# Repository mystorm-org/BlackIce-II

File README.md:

# BlackIce-II

Project documentation can be found in the [project wiki](https://github.com/mystorm-org/BlackIce-II/wiki).

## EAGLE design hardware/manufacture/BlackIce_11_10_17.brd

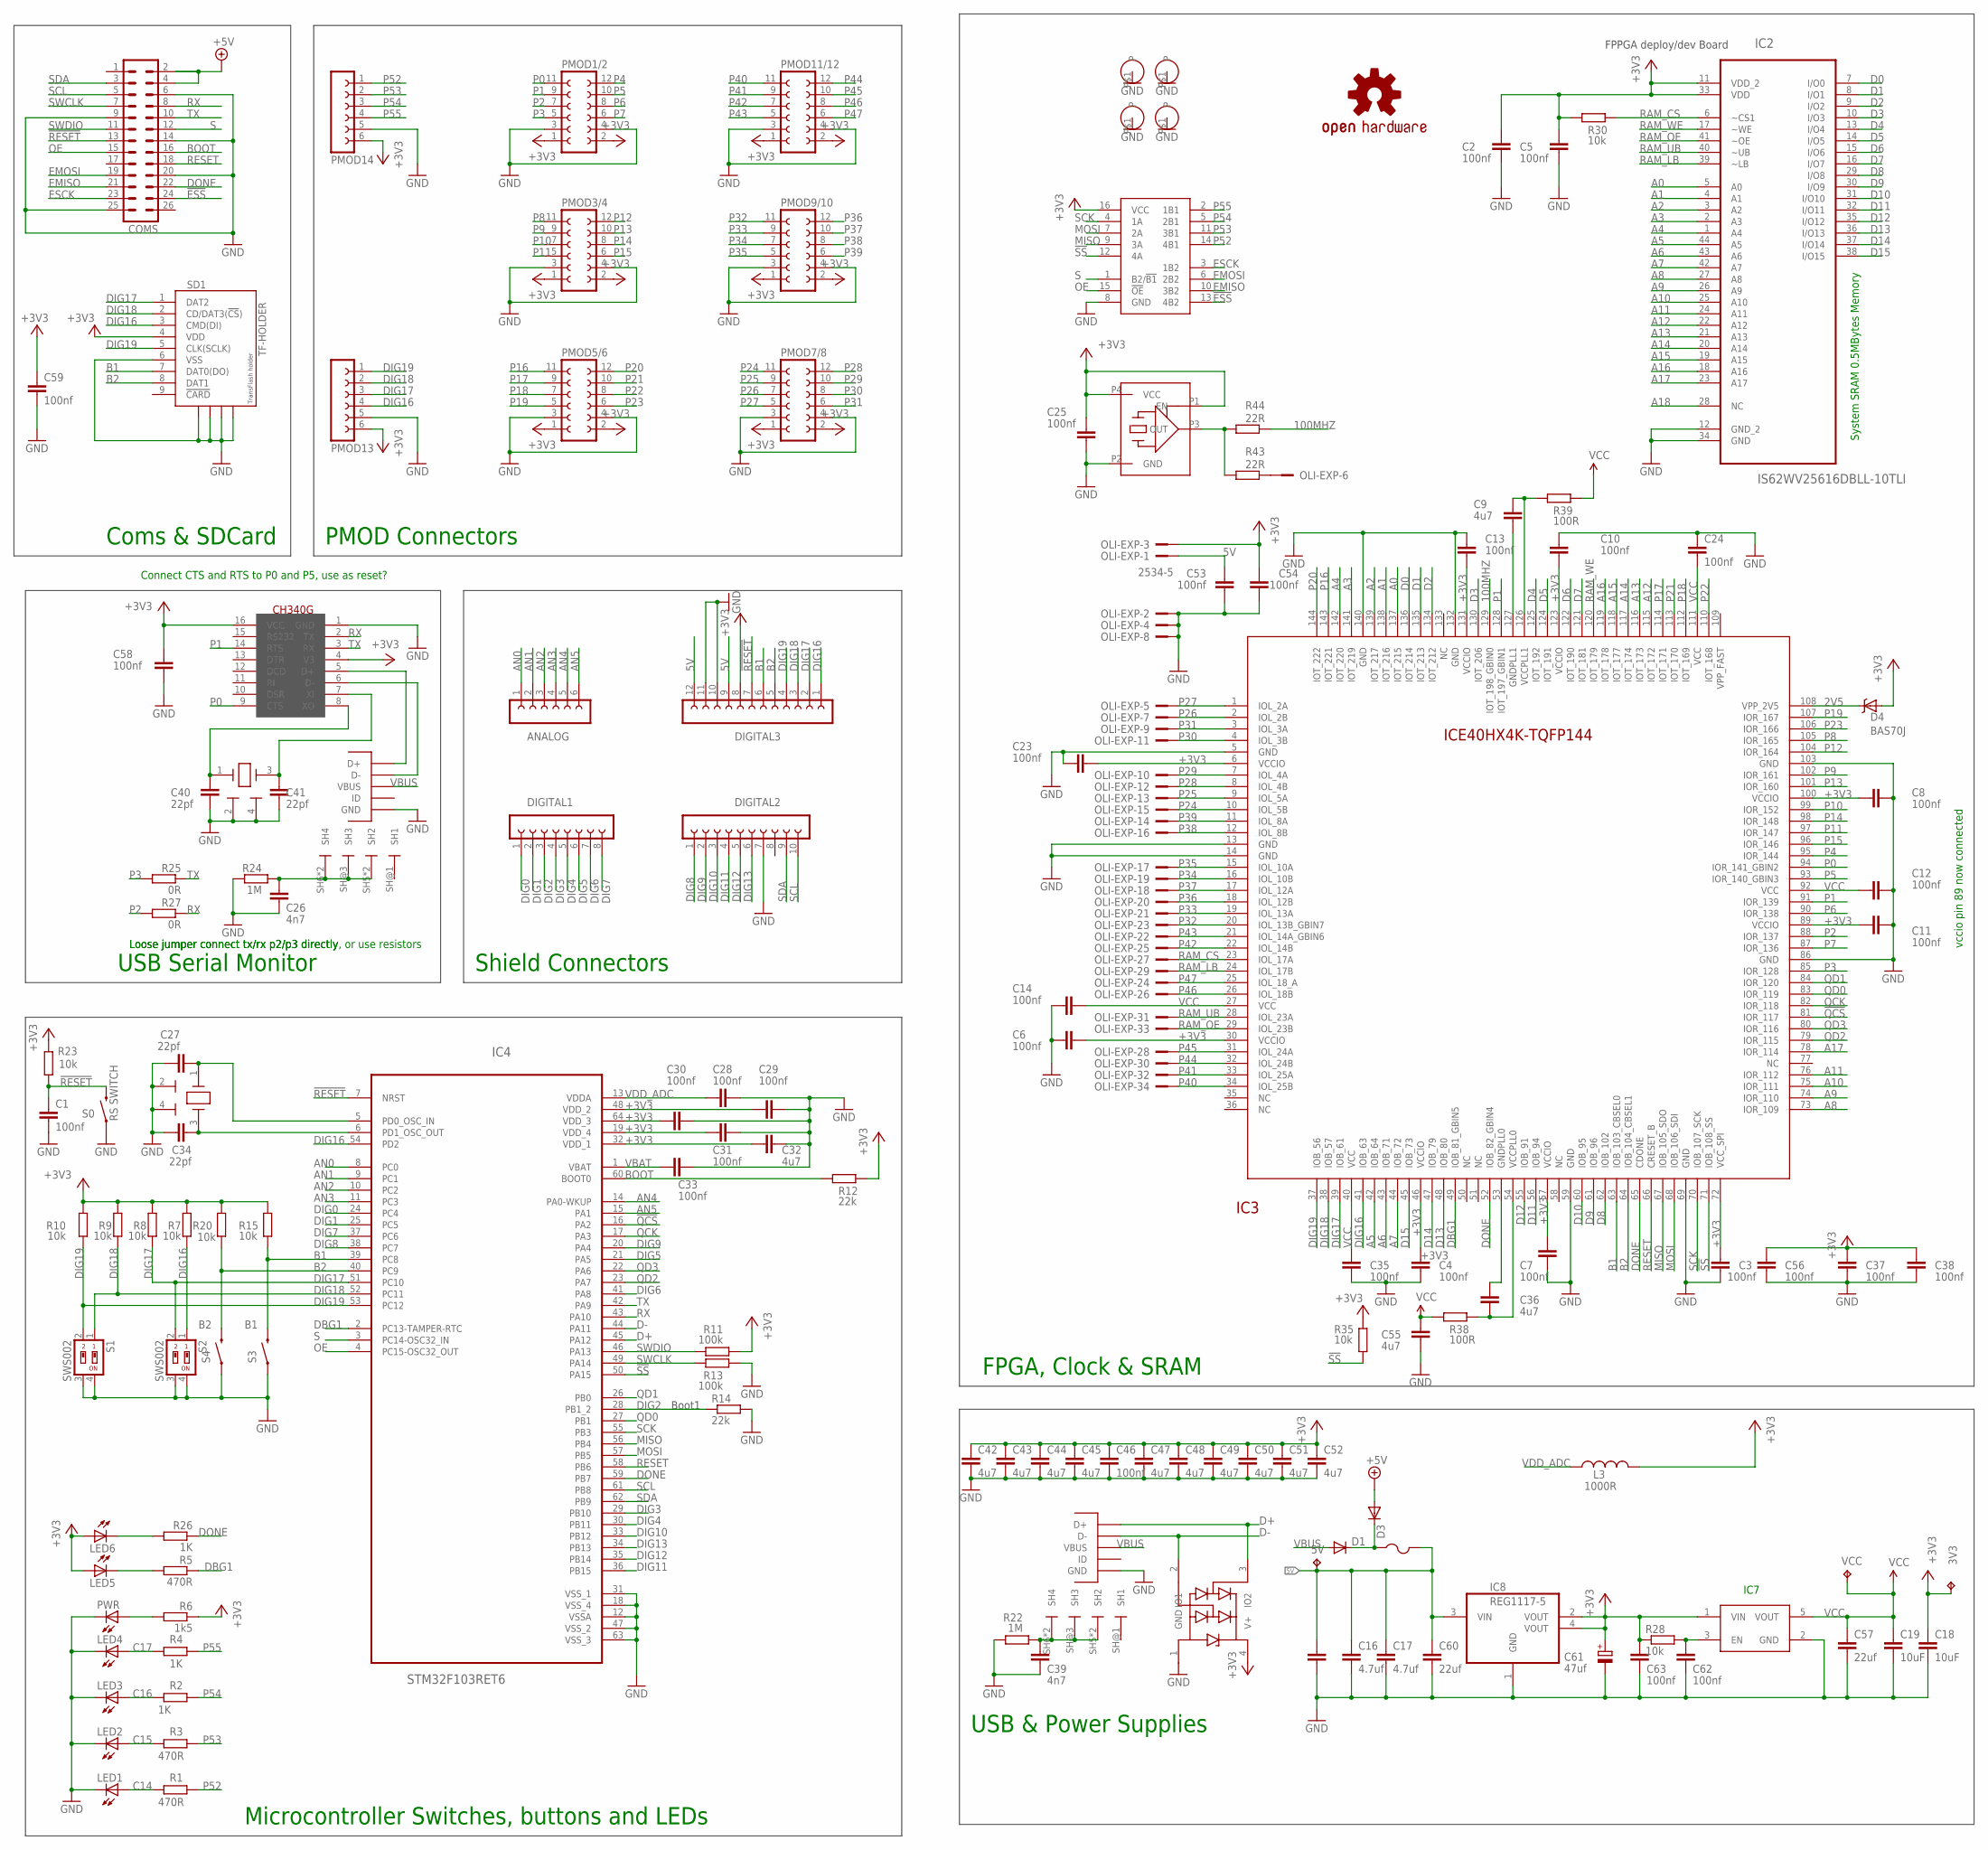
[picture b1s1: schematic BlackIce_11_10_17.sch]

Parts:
3V3, 5V: TPB1,27; B1,27
ANALOG: FE06-1; FE06
C1, C2, C3, C4, C5, C6, C7, C8, C10, C11, C12, C13, C14, C23, C24, C25, C28, C29, C30, C31, C33, C35, C37, C38, C46, C53, C54, C56, C58, C59, C62, C63: 100nf; C0402
C9, C32, C36, C42, C43, C44, C45, C47, C48, C49, C50, C51, C52, C55: 4u7; C0402
C16, C17: 4.7uf; C0402
C18, C19: 10uF; C0603
C20: 47uF; 1206
C26, C39: 4n7; C0402
C27, C34, C40, C41: 22pf; C0402
C57, C60: 22uf; C0603
C61: 47uf; R/2012-12W
COM: FCI-MICROUSB-B-PEG; MICROUSB-B-PEG
COMS: MA13-2
D1, D3: DIODE-SOD123; SOD123
D4: BAS70J; SOD-323
DIGITAL1: FE08-1; FE08
DIGITAL2: FE10-1; FE10
DIGITAL3: FE12-1; FE12
ESD1: PRTR5V0U2X; SOT143B
F1: PTCFUSE-1206; R1206
IC1: CH340G; SOIC16
IC2: IS62WV25616DBLL-10TLI; SOP80P1176X120-44N
IC3: ICE40HX4K_TQFP144; TQFP144
IC4: STM32F103RET6; QFP50P1200X1200X160-64N
IC6: 74CBTLV3257; TSSOP-16
IC7: NCP114; TSOP-5/SOT23-5
IC8: REG1117-5; SOT223
L3: 1000R; C0402
LED1, LED2, LED3, LED4, LED5, LED6: LEDCHIPLED_0603; CHIPLED_0603
OLI-EXP: 2534-5; PAK100/2500-5-34
OSHW: OSHW-LOGOL; OSHW-LOGO-L
PMOD1/2, PMOD3/4, PMOD5/6, PMOD7/8, PMOD9/10, PMOD11/12: FE06-2W
PMOD13, PMOD14: FE06W
PWR: LEDCHIPLED_0603; CHIPLED_0603
R1, R3, R5: 470R; R0402
R2, R4, R26: 1K; R0402
R6: 1k5; R0402
R7, R8, R9, R10, R15, R20, R23, R28, R30, R35: 10k; R0402
R11, R13: 100k; R0402
R12, R14: 22k; R0402
R22, R24: 1M; R0402
R25, R27: 0R; R0402
R38, R39: 100R; R0402
R43, R44: 22R; R0402
S0: RS SWITCH; TACTILE-SWITCH-1101NE
S1, S2: SWS002; SMS-002
S3, S4: SWITCH-MOMENTARY-2SMD-1101NE; TACTILE-SWITCH-1101NE
SD1: TF-HOLDER; TF-PULL
U$2: FCI-MICROUSB-B-PEG; MICROUSB-B-PEG
U$16, U$21, U$22, U$24: HOLE-2.5MM; 2.5MM-HOLE
VCC: TPB1,27; B1,27
X1: TXC-7W-20.000MBB-T; XTAL-7X5
Y1: 12MZ; CRYSTAL-3.2X2.5
Y2: 12Mz; CRYSTAL-3.2X2.5

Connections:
2V5: D4.C, IC3.108 (VPP_2V5)
5V: 5V.TP, C16.1, C17.1, C20.1, C53.1, C60.1, DIGITAL3.9, DIGITAL3.12, F1.2, IC8.3 (VIN), OLI-EXP.1
100MHZ: IC3.129 (IOT_198_GBIN0), R44.2
!ESS: COMS.24, IC6.13 (4B2)
!QCS: IC3.81 (IOR_117), IC4.16 (PA2)
!RESET: C1.1, COMS.13, DIGITAL3.7, IC4.7 (NRST), R23.1, S0.2
!SS: IC3.71 (IOB_108_SS), IC4.50 (PA15), IC6.12 (4A), R35.2
+3V3: 3V3.TP, C2.1, C3.1, C4.1, C5.1, C6.2, C7.1, C8.1, C10.2, C11.1, C13.1, C18.1, C23.1, C25.2, C29.2, C30.2, C31.2, C32.2, C37.1, C38.1, C42.1, C43.1, C44.1, C45.1, C46.1, C47.1, C48.1, C49.1, C50.1, C51.1, C52.1, C54.1, C56.1, C58.2, C59.1, C61.+, C63.2, D4.A, DIGITAL3.8, ESD1.4 (V+), IC1.4 (V3), IC1.16 (VCC), IC2.11 (VDD_2), IC2.33 (VDD), IC3.6 (VCCIO), IC3.30 (VCCIO), IC3.46 (VCCIO), IC3.57 (VCCIO), IC3.72 (VCC_SPI), IC3.89 (VCCIO), IC3.100 (VCCIO), IC3.123 (VCCIO), IC3.131 (VCCIO), IC4.19 (VDD_4), IC4.32 (VDD_1), IC4.48 (VDD_2), IC4.64 (VDD_3), IC6.16 (VCC), IC7.1 (VIN), IC8.2 (VOUT), IC8.4 (VOUT), L3.1, LED5.A, LED6.A, OLI-EXP.3, PMOD1/2.1, PMOD1/2.2, PMOD3/4.1, PMOD3/4.2, PMOD5/6.1, PMOD5/6.2, PMOD7/8.1, PMOD7/8.2, PMOD9/10.1, PMOD9/10.2, PMOD11/12.1, PMOD11/12.2, PMOD13.6, PMOD14.6, R6.1, R7.2, R8.2, R9.2, R10.2, R11.1, R12.2, R15.2, R20.2, R23.2, R28.1, R30.2, R35.1, SD1.4 (VDD), X1.P1 (EN), X1.P4 (VCC)
+5V: COMS.2, COMS.4, D3.A
A0: IC2.5 (A0), IC3.137 (IOT_215)
A1: IC2.4 (A1), IC3.138 (IOT_216)
A2: IC2.3 (A2), IC3.139 (IOT_217)
A3: IC2.2 (A3), IC3.141 (IOT_219)
A4: IC2.1 (A4), IC3.142 (IOT_220)
A5: IC2.44 (A5), IC3.42 (IOB_64)
A6: IC2.43 (A6), IC3.43 (IOB_71)
A7: IC2.42 (A7), IC3.44 (IOB_72)
A8: IC2.27 (A8), IC3.73 (IOR_109)
A9: IC2.26 (A9), IC3.74 (IOR_110)
A10: IC2.25 (A10), IC3.75 (IOR_111)
A11: IC2.24 (A11), IC3.76 (IOR_112)
A12: IC2.22 (A12), IC3.115 (IOT_172)
A13: IC2.21 (A13), IC3.116 (IOT_173)
A14: IC2.20 (A14), IC3.117 (IOT_174)
A15: IC2.19 (A15), IC3.118 (IOT_177)
A16: IC2.18 (A16), IC3.119 (IOT_178)
A17: IC2.23 (A17), IC3.78 (IOR_114)
A18: IC2.28 (NC)
AN0: ANALOG.1, IC4.8 (PC0)
AN1: ANALOG.2, IC4.9 (PC1)
AN2: ANALOG.3, IC4.10 (PC2)
AN3: ANALOG.4, IC4.11 (PC3)
AN4: ANALOG.5, IC4.14 (PA0-WKUP)
AN5: ANALOG.6, IC4.15 (PA1)
B1: DIGITAL3.6, IC3.63 (IOB_103_CBSEL0), IC4.39 (PC8), R15.1, S3.2, SD1.7 (DAT0(DO))
B2: DIGITAL3.5, IC3.64 (IOB_104_CBSEL1), IC4.40 (PC9), R20.1, S4.2, SD1.8 (DAT1)
BOOT: COMS.16, IC4.60 (BOOT0), R12.1
C14: LED1.A, R1.1
C15: LED2.A, R3.1
C16: LED3.A, R2.1
C17: LED4.A, R4.1
D0: IC2.7 (I/O0), IC3.136 (IOT_214)
D1: IC2.8 (I/O1), IC3.135 (IOT_213)
D2: IC2.9 (I/O2), IC3.134 (IOT_212)
D3: IC2.10 (I/O3), IC3.130 (IOT_206)
D4: IC2.13 (I/O4), IC3.125 (IOT_192)
D5: IC2.14 (I/O5), IC3.124 (IOT_191)
D6: IC2.15 (I/O6), IC3.122 (IOT_190)
D7: IC2.16 (I/O7), IC3.121 (IOT_181)
D8: IC2.29 (I/O8), IC3.62 (IOB_102)
D9: IC2.30 (I/O9), IC3.61 (IOB_96)
D10: IC2.31 (I/O10), IC3.60 (IOB_95)
D11: IC2.32 (I/O11), IC3.56 (IOB_94)
D12: IC2.35 (I/O12), IC3.55 (IOB_91)
D13: IC2.36 (I/O13), IC3.48 (IOB_80)
D14: IC2.37 (I/O14), IC3.47 (IOB_79)
D15: IC2.38 (I/O15), IC3.45 (IOB_73)
D+: ESD1.3 (IO2), IC4.45 (PA12), U$2.P$3 (D+)
D-: ESD1.2 (IO1), IC4.44 (PA11), U$2.P$2 (D-)
DBG1: IC3.49 (IOB_81_GBIN5), IC4.2 (PC13-TAMPER-RTC), R5.1
DIG0: DIGITAL1.1, IC4.24 (PC4)
DIG1: DIGITAL1.2, IC4.25 (PC5)
DIG2: DIGITAL1.3, IC4.28 (PB1_2), R14.1
DIG3: DIGITAL1.4, IC4.29 (PB10)
DIG4: DIGITAL1.5, IC4.30 (PB11)
DIG5: DIGITAL1.6, IC4.21 (PA5)
DIG6: DIGITAL1.7, IC4.41 (PA8)
DIG7: DIGITAL1.8, IC4.37 (PC6)
DIG8: DIGITAL2.1, IC4.38 (PC7)
DIG9: DIGITAL2.2, IC4.20 (PA4)
DIG10: DIGITAL2.3, IC4.33 (PB12)
DIG11: DIGITAL2.4, IC4.36 (PB15)
DIG12: DIGITAL2.5, IC4.35 (PB14)
DIG13: DIGITAL2.6, IC4.34 (PB13)
DIG16: DIGITAL3.1, IC3.41 (IOB_63), IC4.54 (PD2), PMOD13.4, R7.1, S2.1, SD1.3 (CMD(DI))
DIG17: DIGITAL3.2, IC3.39 (IOB_61), IC4.51 (PC10), PMOD13.3, R8.1, S2.2, SD1.1 (DAT2)
DIG18: DIGITAL3.3, IC3.38 (IOB_57), IC4.52 (PC11), PMOD13.2, R9.1, S1.1, SD1.2 (CD/DAT3(!CS!))
DIG19: DIGITAL3.4, IC3.37 (IOB_56), IC4.53 (PC12), PMOD13.1, R10.1, S1.2, SD1.5 (CLK(SCLK))
DONE: COMS.22, IC3.52 (IOB_82_GBIN4), IC3.65 (CDONE), IC4.59 (PB7), R26.1
EMISO: COMS.21, IC6.10 (3B2)
EMOSI: COMS.19, IC6.6 (2B2)
ESCK: COMS.23, IC6.3 (1B2)
GND: C1.2, C2.2, C3.2, C4.2, C5.2, C6.1, C7.2, C8.2, C10.1, C11.2, C12.2, C13.2, C14.2, C16.2, C17.2, C18.2, C19.2, C20.2, C23.2, C24.1, C25.1, C26.1, C27.1, C28.1, C29.1, C30.1, C31.1, C32.1, C33.1, C34.1, C35.2, C37.2, C38.2, C39.1, C40.1, C41.1, C42.2, C43.2, C44.2, C45.2, C46.2, C47.2, C48.2, C49.2, C50.2, C51.2, C52.2, C53.2, C54.2, C55.2, C56.2, C57.2, C58.1, C59.2, C60.2, C61.-, C62.1, C63.1, COM.P$5 (GND), COMS.6, COMS.9, COMS.14, COMS.20, COMS.25, DIGITAL2.7, DIGITAL3.10, DIGITAL3.11, ESD1.1 (GND), IC1.1 (GND), IC2.12 (GND_2), IC2.34 (GND), IC3.5 (GND), IC3.13 (GND), IC3.14 (GND), IC3.59 (GND), IC3.69 (GND), IC3.86 (GND), IC3.103 (GND), IC3.132 (GND), IC3.140 (GND), IC4.12 (VSSA), IC4.18 (VSS_4), IC4.31 (VSS_1), IC4.47 (VSS_2), IC4.63 (VSS_3), IC6.8 (GND), IC7.2 (GND), IC8.1 (GND), LED1.C, LED2.C, LED3.C, LED4.C, OLI-EXP.2, OLI-EXP.4, OLI-EXP.8, PMOD1/2.3, PMOD1/2.4, PMOD3/4.3, PMOD3/4.4, PMOD5/6.3, PMOD5/6.4, PMOD7/8.3, PMOD7/8.4, PMOD9/10.3, PMOD9/10.4, PMOD11/12.3, PMOD11/12.4, PMOD13.5, PMOD14.5, PWR.C, R13.1, R14.2, R22.2, R24.2, S0.1, S1.3, S1.4, S2.3, S2.4, S3.1, S4.1, SD1.6 (VSS), SD1.S1, SD1.S2, SD1.S3, SD1.S4, U$2.P$5 (GND), U$16.P$1, U$21.P$1, U$22.P$1, U$24.P$1, X1.P2 (GND), Y1.2 (GND), Y1.4 (GND), Y2.2 (GND), Y2.4 (GND)
MISO: IC3.67 (IOB_105_SDO), IC4.56 (PB4), IC6.9 (3A)
MOSI: IC3.68 (IOB_106_SDI), IC4.57 (PB5), IC6.7 (2A)
unnamed: PWR.A, R6.2
unnamed: LED5.C, R5.2
unnamed: C9.2, IC3.126 (VCCPLL1), R39.2
unnamed: C39.2, R22.1, U$2.SH5 (SH2), U$2.SH6 (SH4), U$2.SH@2 (SH2), U$2.SH@3 (SH3), U$2.SH@4 (SH4)
unnamed: C62.2, IC7.3 (EN), R28.2
unnamed: C36.1, IC3.53 (GNDPLL0)
unnamed: C34.2, IC4.6 (PD1_OSC_OUT), Y1.3 (X2)
unnamed: R43.1, R44.1, X1.P3 (OUT)
unnamed: D1.C, D3.C, F1.1
unnamed: COM.P$3 (D+), IC1.5 (D+)
unnamed: COM.P$2 (D-), IC1.6 (D-)
unnamed: C26.2, COM.SH5 (SH2), COM.SH6 (SH4), COM.SH@2 (SH2), COM.SH@3 (SH3), COM.SH@4 (SH4), R24.1
unnamed: C9.1, IC3.127 (GNDPLL1)
unnamed: OLI-EXP.6, R43.2
unnamed: C36.2, IC3.54 (VCCPLL0), R38.1
unnamed: C27.2, IC4.5 (PD0_OSC_IN), Y1.1 (X1)
unnamed: C41.2, IC1.7 (XI), Y2.3 (X2)
unnamed: C40.2, IC1.8 (XO), Y2.1 (X1)
unnamed: LED6.C, R26.2
OE: COMS.15, IC4.4 (PC15-OSC32_OUT), IC6.15 (!OE)
P0: IC1.9 (CTS), IC3.94 (IOR_141_GBIN2), PMOD1/2.11
P1: IC1.14 (RTS), IC3.91 (IOR_139), IC3.128 (IOT_197_GBIN1), PMOD1/2.9
P2: IC3.88 (IOR_137), PMOD1/2.7, R27.2
P3: IC3.85 (IOR_128), PMOD1/2.5, R25.2
P4: IC3.95 (IOR_144), PMOD1/2.12
P5: IC3.93 (IOR_140_GBIN3), PMOD1/2.10
P6: IC3.90 (IOR_138), PMOD1/2.8
P7: IC3.87 (IOR_136), PMOD1/2.6
P8: IC3.105 (IOR_165), PMOD3/4.11
P9: IC3.102 (IOR_161), PMOD3/4.9
P10: IC3.99 (IOR_152), PMOD3/4.7
P11: IC3.97 (IOR_147), PMOD3/4.5
P12: IC3.104 (IOR_164), PMOD3/4.12
P13: IC3.101 (IOR_160), PMOD3/4.10
P14: IC3.98 (IOR_148), PMOD3/4.8
P15: IC3.96 (IOR_146), PMOD3/4.6
P16: IC3.143 (IOT_221), PMOD5/6.11
P17: IC3.114 (IOT_171), PMOD5/6.9
P18: IC3.112 (IOT_169), PMOD5/6.7
P19: IC3.107 (IOR_167), PMOD5/6.5
P20: IC3.144 (IOT_222), PMOD5/6.12
P21: IC3.113 (IOT_170), PMOD5/6.10
P22: IC3.110 (IOT_168), PMOD5/6.8
P23: IC3.106 (IOR_166), PMOD5/6.6
P24: IC3.10 (IOL_5B), OLI-EXP.15, PMOD7/8.11
P25: IC3.9 (IOL_5A), OLI-EXP.13, PMOD7/8.9
P26: IC3.2 (IOL_2B), OLI-EXP.7, PMOD7/8.7
P27: IC3.1 (IOL_2A), OLI-EXP.5, PMOD7/8.5
P28: IC3.8 (IOL_4B), OLI-EXP.12, PMOD7/8.12
P29: IC3.7 (IOL_4A), OLI-EXP.10, PMOD7/8.10
P30: IC3.4 (IOL_3B), OLI-EXP.11, PMOD7/8.8
P31: IC3.3 (IOL_3A), OLI-EXP.9, PMOD7/8.6
P32: IC3.20 (IOL_13B_GBIN7), OLI-EXP.23, PMOD9/10.11
P33: IC3.19 (IOL_13A), OLI-EXP.21, PMOD9/10.9
P34: IC3.16 (IOL_10B), OLI-EXP.19, PMOD9/10.7
P35: IC3.15 (IOL_10A), OLI-EXP.17, PMOD9/10.5
P36: IC3.18 (IOL_12B), OLI-EXP.20, PMOD9/10.12
P37: IC3.17 (IOL_12A), OLI-EXP.18, PMOD9/10.10
P38: IC3.12 (IOL_8B), OLI-EXP.16, PMOD9/10.8
P39: IC3.11 (IOL_8A), OLI-EXP.14, PMOD9/10.6
P40: IC3.34 (IOL_25B), OLI-EXP.34, PMOD11/12.11
P41: IC3.33 (IOL_25A), OLI-EXP.32, PMOD11/12.9
P42: IC3.22 (IOL_14B), OLI-EXP.25, PMOD11/12.7
P43: IC3.21 (IOL_14A_GBIN6), OLI-EXP.22, PMOD11/12.5
P44: IC3.32 (IOL_24B), OLI-EXP.30, PMOD11/12.12
P45: IC3.31 (IOL_24A), OLI-EXP.28, PMOD11/12.10
P46: IC3.26 (IOL_18B), OLI-EXP.26, PMOD11/12.8
P47: IC3.25 (IOL_18_A), OLI-EXP.24, PMOD11/12.6
P52: IC6.14 (4B1), PMOD14.1, R1.2
P53: IC6.11 (3B1), PMOD14.2, R3.2
P54: IC6.5 (2B1), PMOD14.3, R2.2
P55: IC6.2 (1B1), PMOD14.4, R4.2
QCK: IC3.82 (IOR_118), IC4.17 (PA3)
QD0: IC3.83 (IOR_119), IC4.27 (PB1)
QD1: IC3.84 (IOR_120), IC4.26 (PB0)
QD2: IC3.79 (IOR_115), IC4.23 (PA7)
QD3: IC3.80 (IOR_116), IC4.22 (PA6)
RAM_CS: IC2.6 (~CS1), IC3.23 (IOL_17A), OLI-EXP.27, R30.1
RAM_LB: IC2.39 (~LB), IC3.24 (IOL_17B), OLI-EXP.29
RAM_OE: IC2.41 (~OE), IC3.29 (IOL_23B), OLI-EXP.33
RAM_UB: IC2.40 (~UB), IC3.28 (IOL_23A), OLI-EXP.31
RAM_WE: IC2.17 (~WE), IC3.120 (IOT_179)
RESET: COMS.18, IC3.66 (CRESET_B), IC4.58 (PB6)
RX: COMS.8, IC1.2 (TX), IC4.43 (PA10), R27.1
S: COMS.12, IC4.3 (PC14-OSC32_IN), IC6.1 (B2/!B1)
SCK: IC3.70 (IOB_107_SCK), IC4.55 (PB3), IC6.4 (1A)
SCL: COMS.5, DIGITAL2.10, IC4.61 (PB8)
SDA: COMS.3, DIGITAL2.9, IC4.62 (PB9)
SWCLK: COMS.7, IC4.49 (PA14), R13.2
SWDIO: COMS.11, IC4.46 (PA13), R11.2
TX: COMS.10, IC1.3 (RX), IC4.42 (PA9), R25.1
VBAT: C33.2, IC4.1 (VBAT)
VBUS: COM.P$1 (VBUS), D1.A, U$2.P$1 (VBUS)
VCC: C12.1, C14.1, C19.1, C24.2, C35.1, C55.1, C57.1, IC3.27 (VCC), IC3.40 (VCC), IC3.92 (VCC), IC3.111 (VCC), IC7.5 (VOUT), R38.2, R39.1, VCC.TP
VDD_ADC: C28.2, IC4.13 (VDDA), L3.2

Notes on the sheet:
System SRAM 0.5MBytes Memory
FPPGA deploy/dev Board
Boot1
PMOD Connectors
Shield Connectors
Coms & SDCard
FPGA, Clock & SRAM
USB & Power Supplies
Microcontroller Switches, buttons and LEDs
USB Serial Monitor
vccio pin 89 now connected
Loose jumper connect tx/rx p2/p3 directly
Loose jumper connect tx/rx p2/p3 directly, or use resistors
Connect CTS and RTS to P0 and P5, use as reset?
IC7

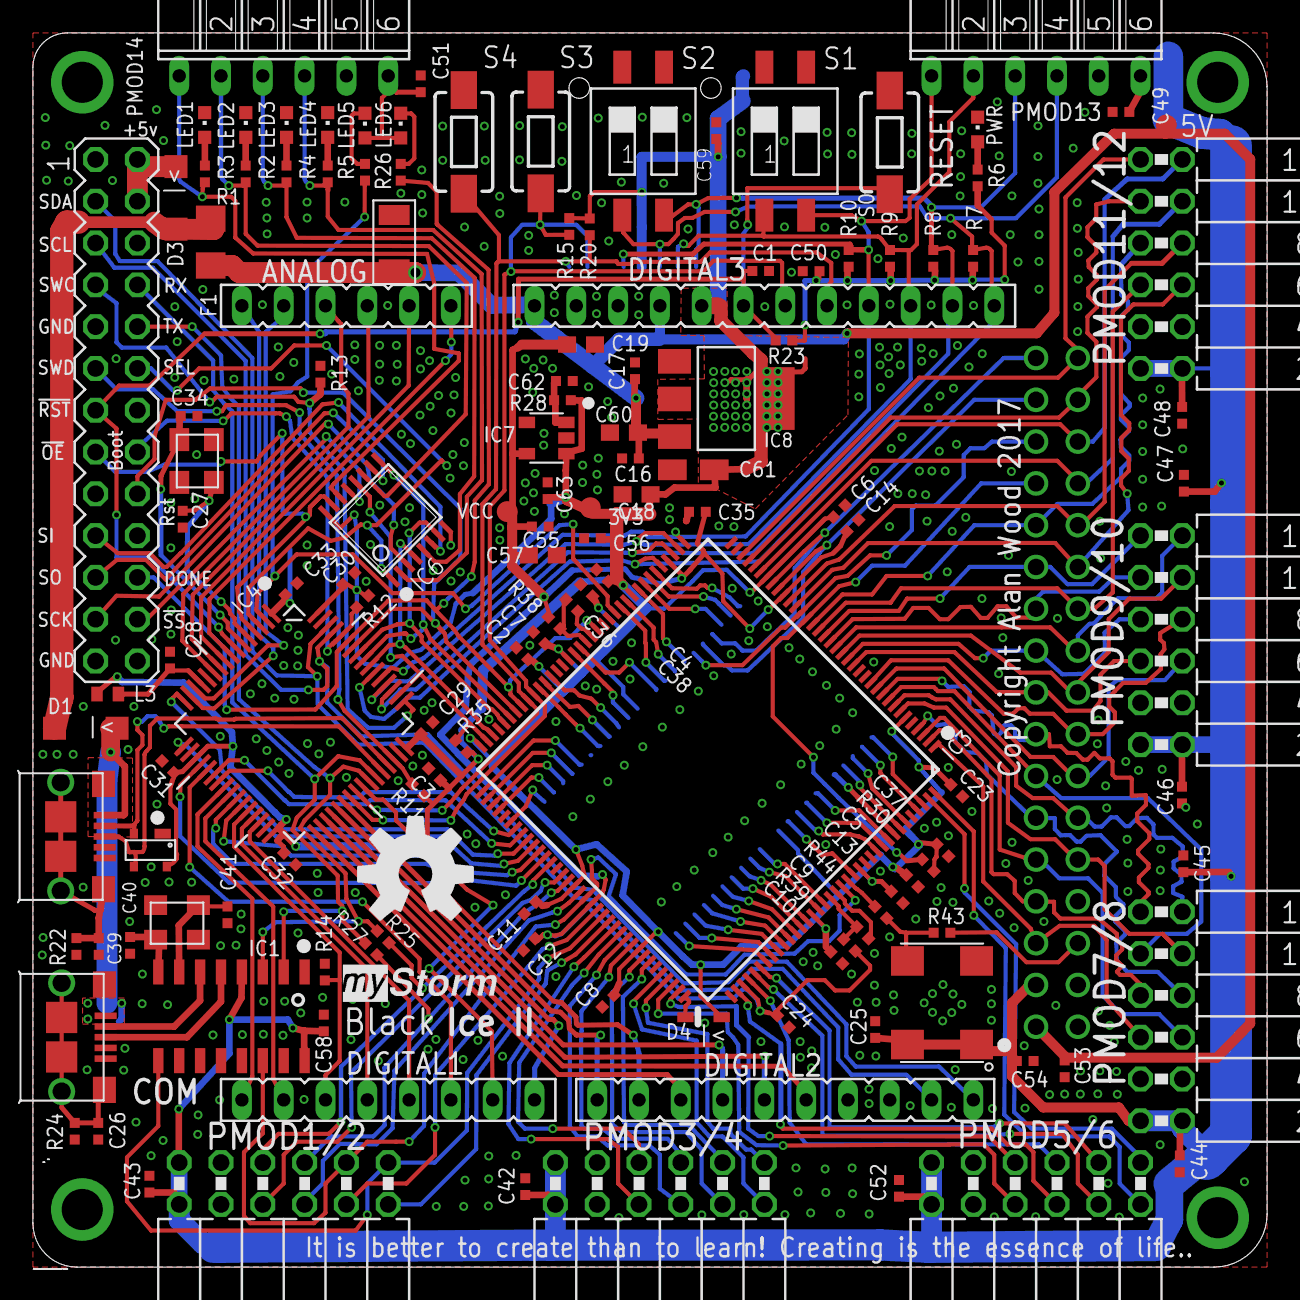
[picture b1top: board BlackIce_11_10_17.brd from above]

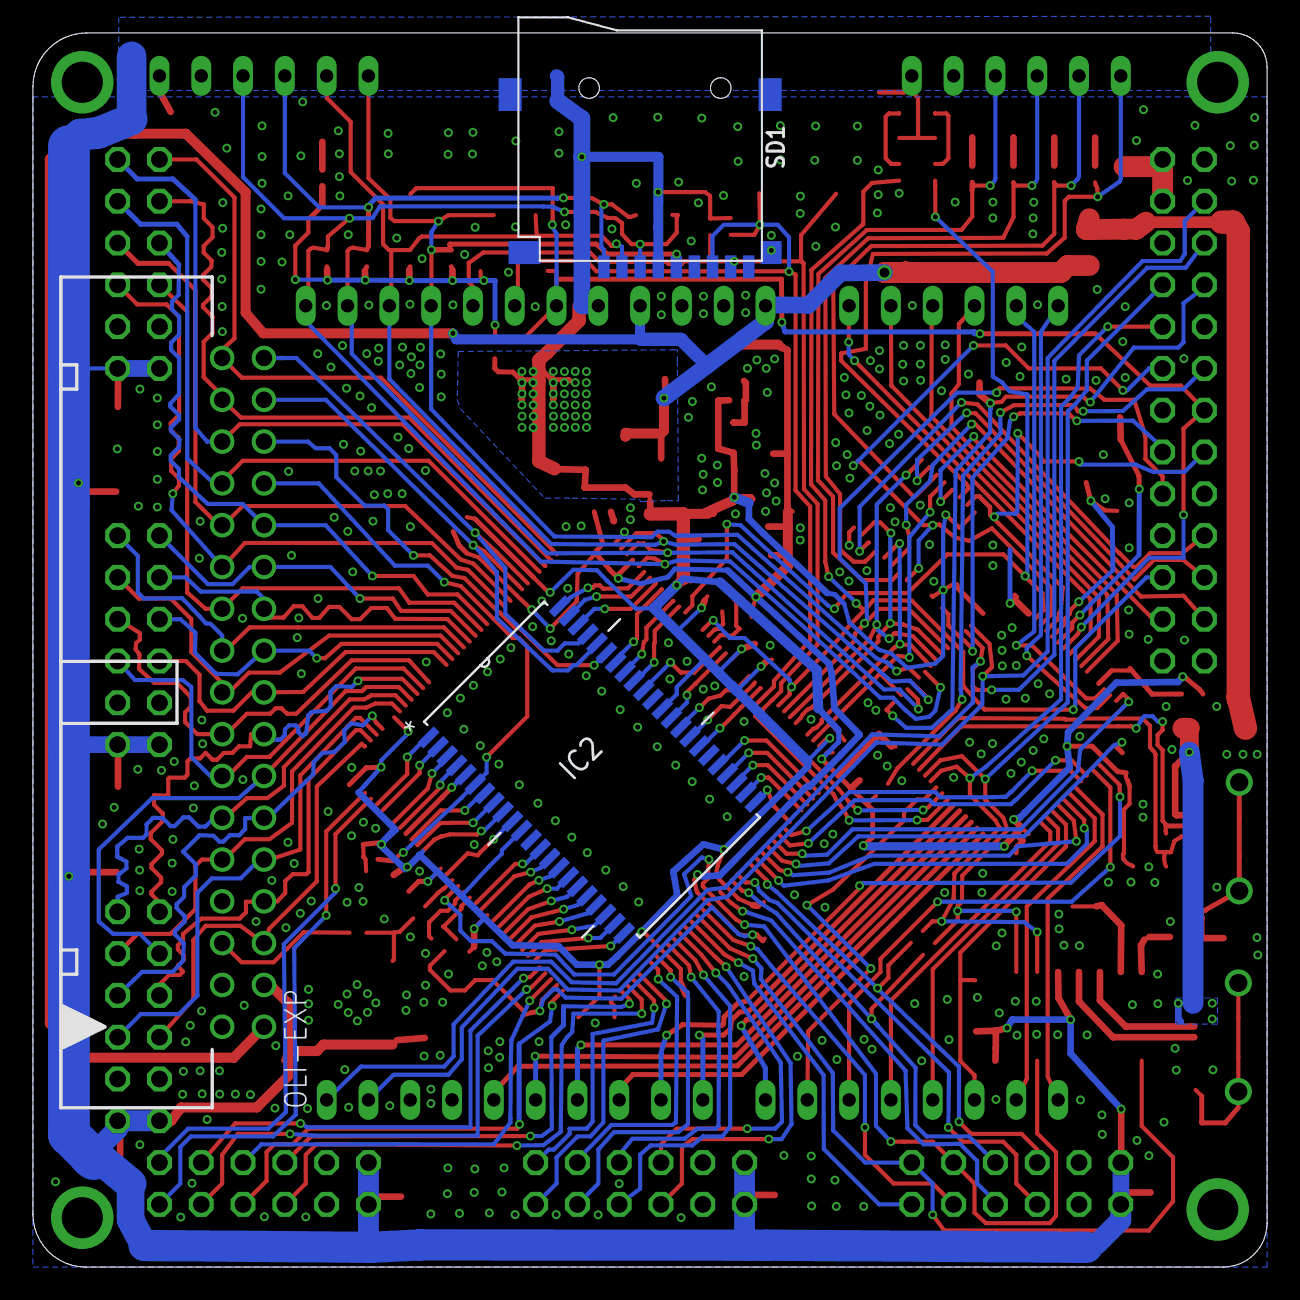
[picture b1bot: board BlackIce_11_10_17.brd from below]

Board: 2 copper layers, 75.0 x 75.0 mm, 142 parts (3 on the bottom side), 179 nets.

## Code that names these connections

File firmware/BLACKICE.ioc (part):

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Mcu.Name=STM32L433R(B-C)Tx
Mcu.Package=LQFP64
Mcu.UserName=STM32L433RCTx
PA0.GPIOParameters=GPIO_Label
PA0.GPIO_Label=AN4
PA0.Signal=GPIO_Input
PA1.GPIOParameters=GPIO_Label
PA1.GPIO_Label=AN5
PA1.Signal=GPIO_Input
PA10.Mode=Asynchronous
PA10.Signal=USART1_RX
PA11.Mode=Device
PA11.Signal=USB_DM
PA12.Mode=Device
PA12.Signal=USB_DP
PA13\ (JTMS-SWDIO).Mode=Serial_Wire
PA13\ (JTMS-SWDIO).Signal=SYS_JTMS-SWDIO
PA14\ (JTCK-SWCLK).Mode=Serial_Wire
PA14\ (JTCK-SWCLK).Signal=SYS_JTCK-SWCLK
PA15\ (JTDI).GPIOParameters=GPIO_Label,PinState
PA15\ (JTDI).GPIO_Label=ICE40_SPI_CS
PA15\ (JTDI).PinState=GPIO_PIN_SET
PA15\ (JTDI).Signal=GPIO_Output
PA2.GPIOParameters=GPIO_Label
PA2.GPIO_Label=QSPI_CS
PA2.Mode=Single Bank 1
PA2.Signal=QUADSPI_BK1_NCS
PA3.GPIOParameters=GPIO_Label
PA3.GPIO_Label=QSPI_CLK
PA3.Mode=Single Bank 1
PA3.Signal=QUADSPI_CLK
PA4.GPIOParameters=GPIO_Label
PA4.GPIO_Label=DIG9
PA4.Signal=GPIO_Input
PA5.GPIOParameters=GPIO_Label
PA5.GPIO_Label=DIG5
PA5.Signal=GPIO_Input
PA6.GPIOParameters=GPIO_Label
PA6.GPIO_Label=QSPI_D3
PA6.Mode=Single Bank 1
PA6.Signal=QUADSPI_BK1_IO3
PA7.GPIOParameters=GPIO_Label
PA7.GPIO_Label=QSPI_D2
PA7.Mode=Single Bank 1
PA7.Signal=QUADSPI_BK1_IO2
PA8.GPIOParameters=GPIO_Label
PA8.GPIO_Label=DIG6
PA8.Signal=GPIO_Input
PA9.Mode=Asynchronous
PA9.Signal=USART1_TX
PB0.GPIOParameters=GPIO_Label
PB0.GPIO_Label=QSPI_D1
PB0.Mode=Single Bank 1
PB0.Signal=QUADSPI_BK1_IO1
PB1.GPIOParameters=GPIO_Label
PB1.GPIO_Label=QSPI_D0
PB1.Mode=Single Bank 1
PB1.Signal=QUADSPI_BK1_IO0
PB10.GPIOParameters=GPIO_Label
PB10.GPIO_Label=DIG3
PB10.Signal=GPIO_Input
PB11.GPIOParameters=GPIO_Label
PB11.GPIO_Label=DIG4
PB11.Signal=GPIO_Input
PB12.GPIOParameters=GPIO_Label
PB12.GPIO_Label=DIG10
PB12.Signal=GPIO_Input
PB13.GPIOParameters=GPIO_Label
PB13.GPIO_Label=DIG13
PB13.Signal=GPIO_Input
PB14.GPIOParameters=GPIO_Label
PB14.GPIO_Label=DIG12
PB14.Signal=GPIO_Input
PB15.GPIOParameters=GPIO_Label
PB15.GPIO_Label=DIG11
PB15.Signal=GPIO_Input
PB2.GPIOParameters=GPIO_Label
PB2.GPIO_Label=DIG2
PB2.Signal=GPIO_Input
PB3\ (JTDO-TRACESWO).Mode=Full_Duplex_Master
PB3\ (JTDO-TRACESWO).Signal=SPI3_SCK
PB4\ (NJTRST).Mode=Full_Duplex_Master
PB4\ (NJTRST).Signal=SPI3_MISO
PB5.Mode=Full_Duplex_Master
PB5.Signal=SPI3_MOSI
PB6.GPIOParameters=GPIO_Label,PinState
PB6.GPIO_Label=ICE40_CRST
PB6.PinState=GPIO_PIN_SET
PB6.Signal=GPIO_Output
PB7.GPIOParameters=GPIO_Label,GPIO_PuPd
PB7.GPIO_Label=ICE40_CDONE
PB7.GPIO_PuPd=GPIO_PULLUP
PB7.Signal=GPIO_Input
PB8.Mode=I2C
PB8.Signal=I2C1_SCL
PB9.Mode=I2C
PB9.Signal=I2C1_SDA
PC0.GPIOParameters=GPIO_Label
PC0.GPIO_Label=AN0
PC0.Signal=GPIO_Input
PC1.GPIOParameters=GPIO_Label
PC1.GPIO_Label=AN1
PC1.Signal=GPIO_Input
PC10.GPIOParameters=GPIO_Label
PC10.GPIO_Label=DIG17
PC10.Signal=GPIO_Input
PC11.GPIOParameters=GPIO_Label
PC11.GPIO_Label=DIG18
PC11.Signal=GPIO_Input
PC12.GPIOParameters=GPIO_Label
PC12.GPIO_Label=DIG19
PC12.Signal=GPIO_Input
PC13.GPIOParameters=GPIO_Label
PC13.GPIO_Label=LED5
PC13.Signal=GPIO_Output
PC14-OSC32_IN\ (PC14).GPIOParameters=GPIO_Label
PC14-OSC32_IN\ (PC14).GPIO_Label=SPI3_MUX_S
PC14-OSC32_IN\ (PC14).Signal=GPIO_Output
PC15-OSC32_OUT\ (PC15).GPIOParameters=GPIO_Label
PC15-OSC32_OUT\ (PC15).GPIO_Label=SPI3_MUX_OE
PC15-OSC32_OUT\ (PC15).Signal=GPIO_Output
PC2.GPIOParameters=GPIO_Label
PC2.GPIO_Label=AN2
PC2.Signal=GPIO_Input
PC3.GPIOParameters=GPIO_Label
PC3.GPIO_Label=AN3
PC3.Signal=GPIO_Input
PC4.GPIOParameters=GPIO_Label
PC4.GPIO_Label=DIG0
PC4.Signal=GPIO_Input
PC5.GPIOParameters=GPIO_Label
PC5.GPIO_Label=DIG1
PC5.Signal=GPIO_Input
PC6.GPIOParameters=GPIO_Label
PC6.GPIO_Label=DIG7
PC6.Signal=GPIO_Input
PC7.GPIOParameters=GPIO_Label
PC7.GPIO_Label=DIG8
PC7.Signal=GPIO_Input
PC8.GPIOParameters=GPIO_Label
PC8.GPIO_Label=B1
PC8.Signal=GPIO_Input
PC9.GPIOParameters=GPIO_Label
PC9.GPIO_Label=B2
PC9.Signal=GPIO_Input
PD2.GPIOParameters=GPIO_Label
PD2.GPIO_Label=DIG16
PD2.Signal=GPIO_Input
PH0-OSC_IN\ (PH0).Mode=HSE-External-Oscillator
PH0-OSC_IN\ (PH0).Signal=RCC_OSC_IN
PH1-OSC_OUT\ (PH1).Mode=HSE-External-Oscillator
PH1-OSC_OUT\ (PH1).Signal=RCC_OSC_OUT
RCC.HSE_VALUE=12000000
RCC.SYSCLKFreq_VALUE=80000000
RCC.SYSCLKSource=RCC_SYSCLKSOURCE_PLLCLK
board=BLACKICE

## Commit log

2017-12-23 Added blackIce-II version of iceboot (0.4) , sourcecode and hardware etc..
2017-12-23 Changed version number of Iceboot
2017-12-23 Updated Iceboot binary
2017-12-23 Updated Iceboot raw
2017-12-23 Updated Iceboot ouput files hex and raw
2017-12-23 Update tutorials to use common PCF file, updated BlackIce-II pcf file, fixed button tutorials
2018-02-21 Change ADR[18:0] to ADR[17:0]
2018-02-24 Add pin definitions for quad SPI pins.
2018-02-24 Change upload device from /dev/ttyUSB0 to /dev/ttyACM0
2018-02-25 Fix typo
2018-02-25 hello world uart_tx example
2018-02-26 Simplify by removing tx_baud_tick
2018-02-27 Update readme.
2018-02-27 uart_loopback example
2018-02-27 Add uart_loopback
2018-03-02 .gitignore
2018-03-05 SRAM example works.
2018-03-05 Refactor chip.v into sram_top and ram_test
2018-03-05 Add copyright headers
2018-03-05 Comments
2018-03-05 Remove UART from SRAM example.
2018-03-05 Explanation waveforms
2018-03-05 Tabs.
2018-03-05 Documentation.
2018-03-05 Remove uart blocks.
2018-03-05 Button 2 corrupts the SRAM read data
2018-03-10 Connect UART_CTS. Remove RTS contention.
2018-03-10 PLL example
2018-03-16 Update README.md
    Link to wiki.
2018-03-16 Move PLL documentation to wiki.
2018-03-17 Pll advanced (#19)
    * More PLL examples
    * Readme
2018-03-18 Pll advanced (#20)
    * More PLL examples
    * Readme
    * More PLL examples
2018-03-18 Pll advanced (#20) (#21)
    * More PLL examples
    * Readme
    * More PLL examples
2018-03-24 Fix the comment: the oscillator is actually 100 Mhz

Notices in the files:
hardware/manufacture/BlackIce_11_10_17.brd:
Copyright Alan Wood 2017
parts and their libraries:
SparkFun-Passives: Licensing: Creative Commons ShareAlike 4.0 International - https://creativecommons.org/licenses/by-sa/4.0
